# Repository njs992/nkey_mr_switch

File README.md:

# It's a tester. For keyswitches. Named Mr. Switch.
All the pcb and plate files are for KiCad. The plate is just a pcb with no wires.
I ordered stuff from JLCPCB.com. They did a good job, but the plate isn't going to be as cheap as when you order it because of the increased manufacturing time. They'll contact you afterward. It was still pretty cheap.
I use Kailh hotswap sockets and the Adafruit reverse mount LEDs. Currently I've used a SAMD51 Seeduino Xiao, but I think one of the RP2040 ones would be a better fit, as that should make it QMK compatible (with some custom work, obv).
The firmware is garbage right now :) No HID code, debounce issues, LED address issues... It's a work in progress.

# HAVE FUN :)

If you want to use it please leave Mr. Switch's face somewhere on there.
Maybe also give me a shoutout.

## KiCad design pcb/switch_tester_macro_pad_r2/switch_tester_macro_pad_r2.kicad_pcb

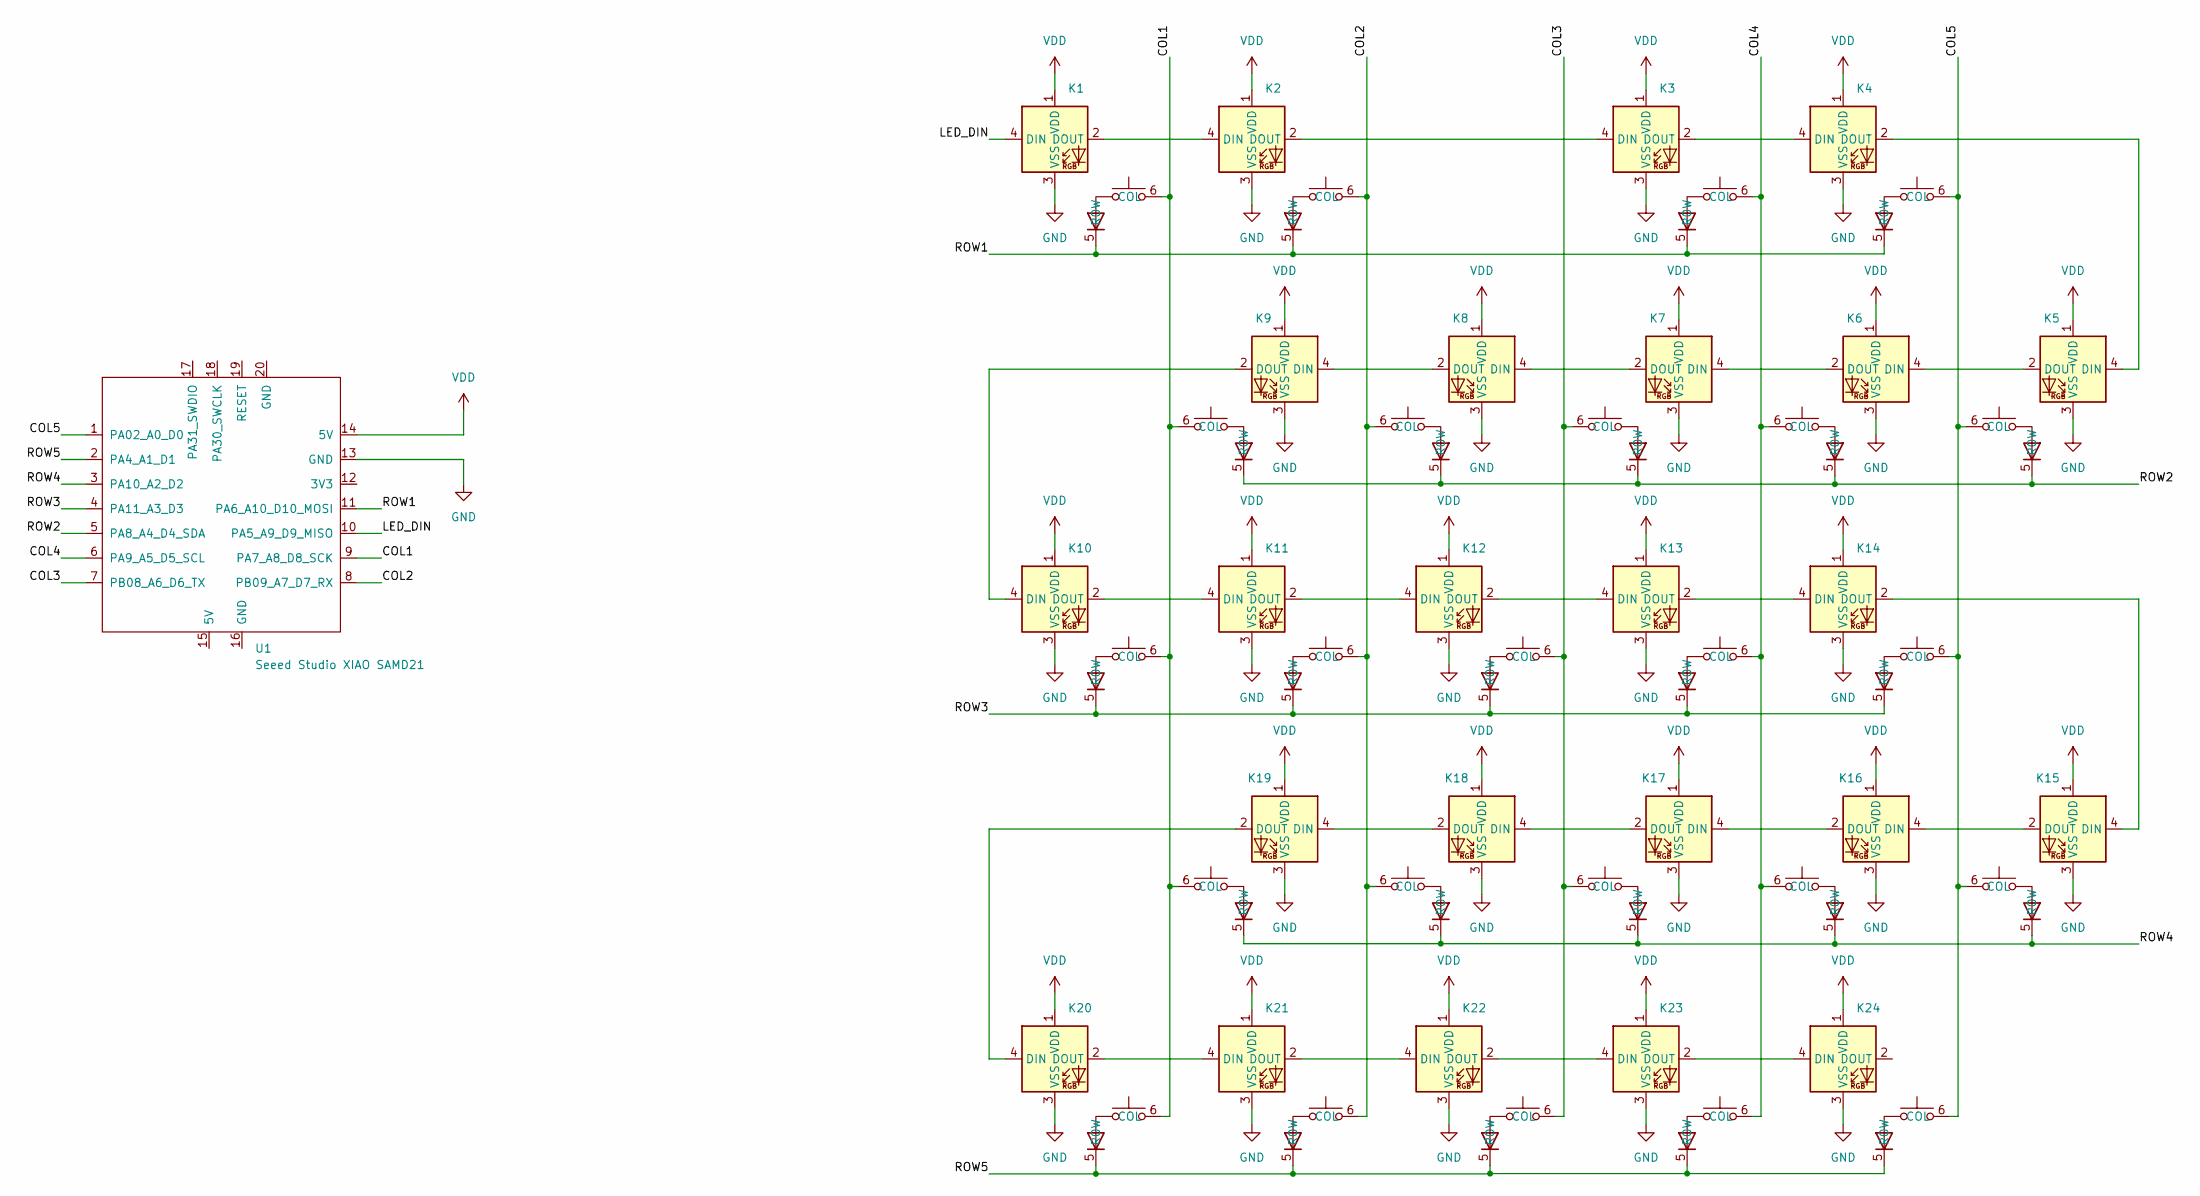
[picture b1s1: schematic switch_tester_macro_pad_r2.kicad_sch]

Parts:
K1, K2, K3, K4, K10, K11, K12, K13, K14, K20, K21, K22, K23, K24: 1U_hl
K5, K6, K7, K8, K9, K15, K16, K17, K18, K19: 1U_hl_backwards
U1: Seeed Studio XIAO SAMD21; XIAO-SAMD21-RP2040-14P-2.54-21X17.8MM (Seeeduino XIAO)

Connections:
/COL1: K1.6 (COL), K9.6 (COL), K10.6 (COL), K19.6 (COL), K20.6 (COL), U1.9 (PA7_A8_D8_SCK)
/COL2: K2.6 (COL), K8.6 (COL), K11.6 (COL), K18.6 (COL), K21.6 (COL), U1.8 (PB09_A7_D7_RX)
/COL3: K7.6 (COL), K12.6 (COL), K17.6 (COL), K22.6 (COL), U1.7 (PB08_A6_D6_TX)
/COL4: K3.6 (COL), K6.6 (COL), K13.6 (COL), K16.6 (COL), K23.6 (COL), U1.6 (PA9_A5_D5_SCL)
/COL5: K4.6 (COL), K5.6 (COL), K14.6 (COL), K15.6 (COL), K24.6 (COL), U1.1 (PA02_A0_D0)
/LED_DIN: K1.4 (DIN), U1.10 (PA5_A9_D9_MISO)
/ROW1: K1.5 (ROW), K2.5 (ROW), K3.5 (ROW), K4.5 (ROW), U1.11 (PA6_A10_D10_MOSI)
/ROW2: K5.5 (ROW), K6.5 (ROW), K7.5 (ROW), K8.5 (ROW), K9.5 (ROW), U1.5 (PA8_A4_D4_SDA)
/ROW3: K10.5 (ROW), K11.5 (ROW), K12.5 (ROW), K13.5 (ROW), K14.5 (ROW), U1.4 (PA11_A3_D3)
/ROW4: K15.5 (ROW), K16.5 (ROW), K17.5 (ROW), K18.5 (ROW), K19.5 (ROW), U1.3 (PA10_A2_D2)
/ROW5: K20.5 (ROW), K21.5 (ROW), K22.5 (ROW), K23.5 (ROW), K24.5 (ROW), U1.2 (PA4_A1_D1)
GND: K1.3 (VSS), K2.3 (VSS), K3.3 (VSS), K4.3 (VSS), K5.3 (VSS), K6.3 (VSS), K7.3 (VSS), K8.3 (VSS), K9.3 (VSS), K10.3 (VSS), K11.3 (VSS), K12.3 (VSS), K13.3 (VSS), K14.3 (VSS), K15.3 (VSS), K16.3 (VSS), K17.3 (VSS), K18.3 (VSS), K19.3 (VSS), K20.3 (VSS), K21.3 (VSS), K22.3 (VSS), K23.3 (VSS), K24.3 (VSS), U1.13 (GND)
unnamed: K1.2 (DOUT), K2.4 (DIN)
unnamed: K2.2 (DOUT), K3.4 (DIN)
unnamed: K3.2 (DOUT), K4.4 (DIN)
unnamed: K4.2 (DOUT), K5.4 (DIN)
unnamed: K5.2 (DOUT), K6.4 (DIN)
unnamed: K6.2 (DOUT), K7.4 (DIN)
unnamed: K7.2 (DOUT), K8.4 (DIN)
unnamed: K8.2 (DOUT), K9.4 (DIN)
unnamed: K9.2 (DOUT), K10.4 (DIN)
unnamed: K10.2 (DOUT), K11.4 (DIN)
unnamed: K11.2 (DOUT), K12.4 (DIN)
unnamed: K12.2 (DOUT), K13.4 (DIN)
unnamed: K13.2 (DOUT), K14.4 (DIN)
unnamed: K14.2 (DOUT), K15.4 (DIN)
unnamed: K15.2 (DOUT), K16.4 (DIN)
unnamed: K16.2 (DOUT), K17.4 (DIN)
unnamed: K17.2 (DOUT), K18.4 (DIN)
unnamed: K18.2 (DOUT), K19.4 (DIN)
unnamed: K19.2 (DOUT), K20.4 (DIN)
unnamed: K20.2 (DOUT), K21.4 (DIN)
unnamed: K21.2 (DOUT), K22.4 (DIN)
unnamed: K22.2 (DOUT), K23.4 (DIN)
unnamed: K23.2 (DOUT), K24.4 (DIN)
VDD: K1.1 (VDD), K2.1 (VDD), K3.1 (VDD), K4.1 (VDD), K5.1 (VDD), K6.1 (VDD), K7.1 (VDD), K8.1 (VDD), K9.1 (VDD), K10.1 (VDD), K11.1 (VDD), K12.1 (VDD), K13.1 (VDD), K14.1 (VDD), K15.1 (VDD), K16.1 (VDD), K17.1 (VDD), K18.1 (VDD), K19.1 (VDD), K20.1 (VDD), K21.1 (VDD), K22.1 (VDD), K23.1 (VDD), K24.1 (VDD), U1.14 (5V)

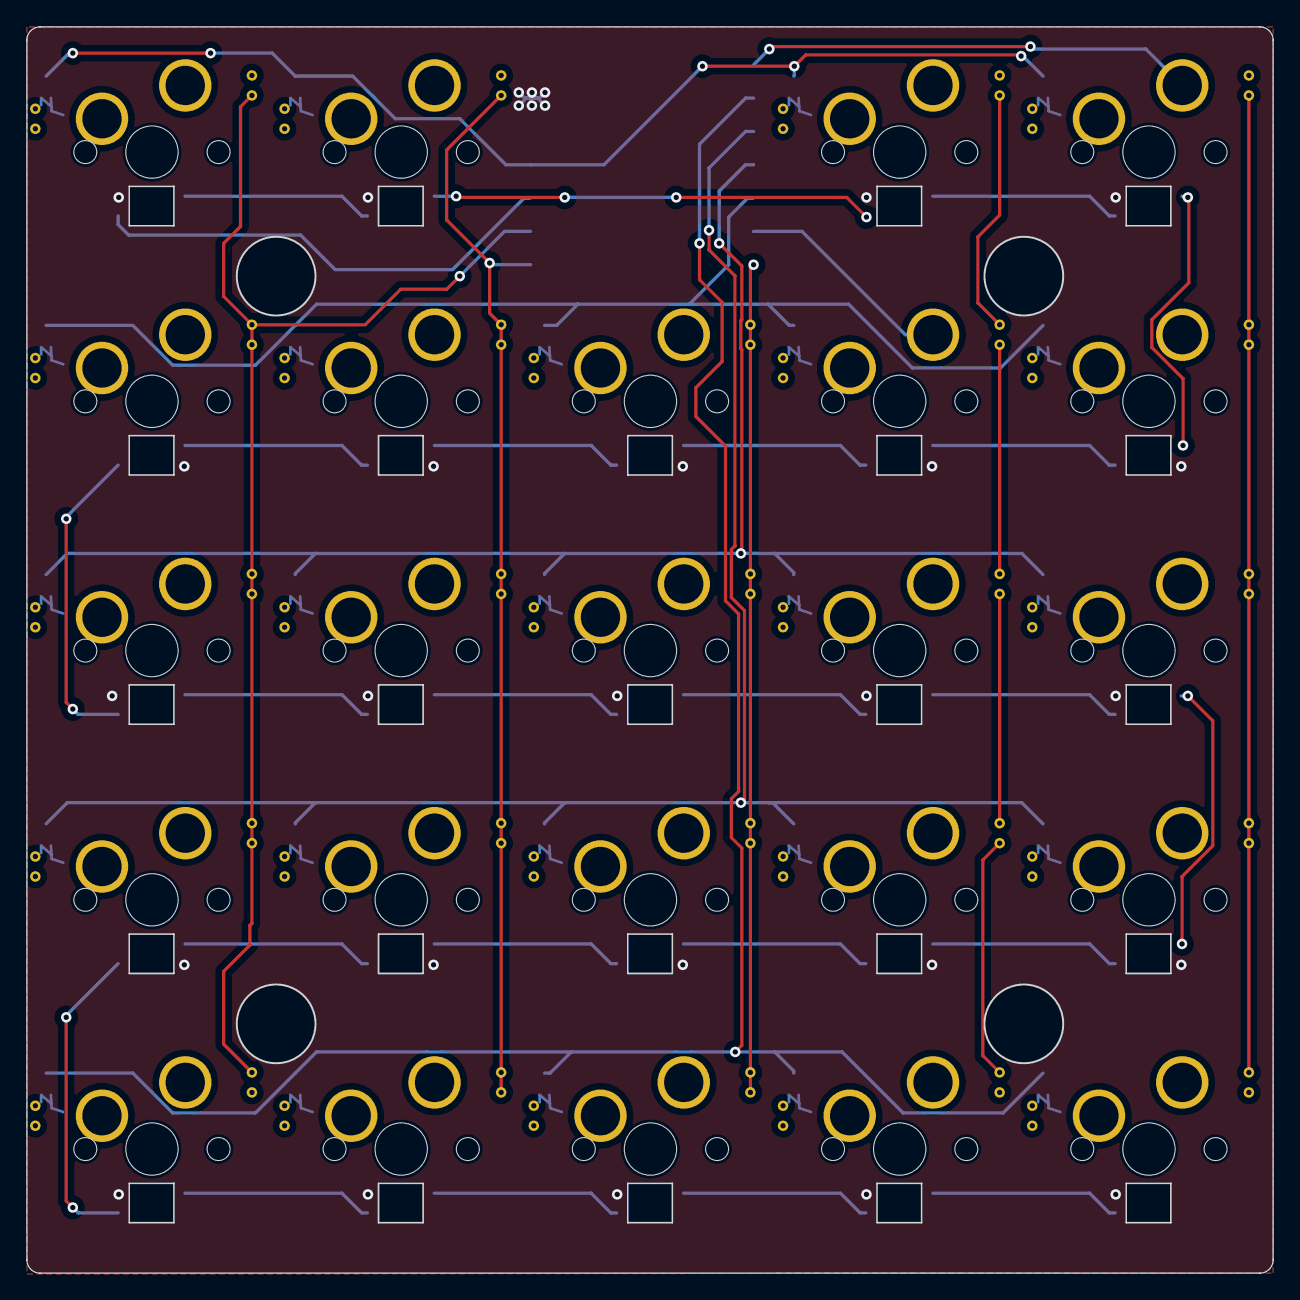
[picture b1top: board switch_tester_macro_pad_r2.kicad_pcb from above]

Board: 2 copper layers, 95.0 x 94.9 mm, 25 parts (1 on the bottom side), 36 nets.

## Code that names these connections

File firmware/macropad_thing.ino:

#include <FastLED.h>
#include <array>
#include <unordered_map>

// Row and Column pin definitions
#define NUM_KEYS 24
#define ROW1 10
#define ROW2 4
#define ROW3 3
#define ROW4 2
#define ROW5 1
#define COL1 8
#define COL2 7
#define COL3 6
#define COL4 5
#define COL5 0

CRGB all_the_colors[] = {
  CRGB::AliceBlue,
  CRGB::Amethyst,
  CRGB::AntiqueWhite,
  CRGB::Aqua,
  CRGB::Aquamarine,
  CRGB::Azure,
  CRGB::Beige,
  CRGB::Bisque,
  CRGB::Black,
  CRGB::BlanchedAlmond,
  CRGB::Blue,
  CRGB::BlueViolet,
  CRGB::Brown,
  CRGB::BurlyWood,
  CRGB::CadetBlue,
  CRGB::Chartreuse,
  CRGB::Chocolate,
  CRGB::Coral,
  CRGB::CornflowerBlue,
  CRGB::Cornsilk,
  CRGB::Crimson,
  CRGB::Cyan,
  CRGB::DarkBlue,
  CRGB::DarkCyan,
  CRGB::DarkGoldenrod,
  CRGB::DarkGray,
  CRGB::DarkGrey,
  CRGB::DarkGreen,
  CRGB::DarkKhaki,
  CRGB::DarkMagenta,
  CRGB::DarkOliveGreen,
  CRGB::DarkOrange,
  CRGB::DarkOrchid,
  CRGB::DarkRed,
  CRGB::DarkSalmon,
  CRGB::DarkSeaGreen,
  CRGB::DarkSlateBlue,
  CRGB::DarkSlateGray,
  CRGB::DarkSlateGrey,
  CRGB::DarkTurquoise,
  CRGB::DarkViolet,
  CRGB::DeepPink,
  CRGB::DeepSkyBlue,
  CRGB::DimGray,
  CRGB::DimGrey,
  CRGB::DodgerBlue,
  CRGB::FireBrick,
  CRGB::FloralWhite,
  CRGB::ForestGreen,
  CRGB::Fuchsia,
  CRGB::Gainsboro,
  CRGB::GhostWhite,
  CRGB::Gold,
  CRGB::Goldenrod,
  CRGB::Gray,
  CRGB::Grey,
  CRGB::Green,
  CRGB::GreenYellow,
  CRGB::Honeydew,
  CRGB::HotPink,
  CRGB::IndianRed,
  CRGB::Indigo,
  CRGB::Ivory,
  CRGB::Khaki,
  CRGB::Lavender,
  CRGB::LavenderBlush,
  CRGB::LawnGreen,
  CRGB::LemonChiffon,
  CRGB::LightBlue,
  CRGB::LightCoral,
  CRGB::LightCyan,
  CRGB::LightGoldenrodYellow,
  CRGB::LightGreen,
  CRGB::LightGrey,
  CRGB::LightPink,
  CRGB::LightSalmon,
  CRGB::LightSeaGreen,
  CRGB::LightSkyBlue,
  CRGB::LightSlateGray,
  CRGB::LightSlateGrey,
  CRGB::LightSteelBlue,
  CRGB::LightYellow,
  CRGB::Lime,
  CRGB::LimeGreen,
  CRGB::Linen,
  CRGB::Magenta,
  CRGB::Maroon,
  CRGB::MediumAquamarine,
  CRGB::MediumBlue,
  CRGB::MediumOrchid,
  CRGB::MediumPurple,
  CRGB::MediumSeaGreen,
  CRGB::MediumSlateBlue,
  CRGB::MediumSpringGreen,
  CRGB::MediumTurquoise,
  CRGB::MediumVioletRed,
  CRGB::MidnightBlue,
  CRGB::MintCream,
  CRGB::MistyRose,
  CRGB::Moccasin,
  CRGB::NavajoWhite,
  CRGB::Navy,
  CRGB::OldLace,
  CRGB::Olive,
  CRGB::OliveDrab,
  CRGB::Orange,
  CRGB::OrangeRed,
  CRGB::Orchid,
  CRGB::PaleGoldenrod,
  CRGB::PaleGreen,
  CRGB::PaleTurquoise,
  CRGB::PaleVioletRed,
  CRGB::PapayaWhip,
  CRGB::PeachPuff,
  CRGB::Peru,
  CRGB::Pink,
  CRGB::Plaid,
  CRGB::Plum,
  CRGB::PowderBlue,
  CRGB::Purple,
  CRGB::Red,
  CRGB::RosyBrown,
  CRGB::RoyalBlue,
  CRGB::SaddleBrown,
  CRGB::Salmon,
  CRGB::SandyBrown,
  CRGB::SeaGreen,
  CRGB::Seashell,
  CRGB::Sienna,
  CRGB::Silver,
  CRGB::SkyBlue,
  CRGB::SlateBlue,
  CRGB::SlateGray,
  CRGB::SlateGrey,
  CRGB::Snow,
  CRGB::SpringGreen,
  CRGB::SteelBlue,
  CRGB::Tan,
  CRGB::Teal,
  CRGB::Thistle,
  CRGB::Tomato,
  CRGB::Turquoise,
  CRGB::Violet,
  CRGB::Wheat,
  CRGB::White,
  CRGB::WhiteSmoke,
  CRGB::Yellow,
  CRGB::YellowGreen
};

const std::array< int, 5 > columns =   { COL1, COL2, COL3, COL4, COL5 };
const std::array< int, 5 > rows = { ROW1, ROW2, ROW3, ROW4, ROW5 };
// const std::array< int, NUM_KEYS > row_order_thing = { ROW1, ROW2,       ROW4, ROW5,
//                                                       ROW5, ROW4, ROW3, ROW2, ROW1,
//                                                       ROW1, ROW2, ROW3, ROW4, ROW5,
//                                                       ROW5, ROW4, ROW3, ROW2, ROW1,
//                                                       ROW1, ROW2, ROW3, ROW4, ROW5 };

int key_idxs[NUM_KEYS] = {0,8,9,18,19,
                          1,7,10,17,20,
                            6,11,16,21,
                          2,5,12,15,22,
                          3,4,13,14,23
                          };

CRGB key_color[NUM_KEYS] = {
  CRGB::Azure,
  CRGB::BlueViolet,
  CRGB::Chocolate,
  CRGB::Crimson,
  CRGB::DeepPink,
  CRGB::Fuchsia,
  CRGB::Goldenrod,
  CRGB::Green,
  CRGB::Indigo,
  CRGB::Lavender,
  CRGB::LimeGreen,
  CRGB::Magenta,
  CRGB::MintCream,
  CRGB::Orange,
  CRGB::PapayaWhip,
  CRGB::Purple,
  CRGB::SteelBlue,
  CRGB::Teal,
  CRGB::Tomato,
  CRGB::Turquoise,
  CRGB::Violet,
  CRGB::Yellow,
  CRGB::Red,
  CRGB::Blue
};

bool key_status[NUM_KEYS];

// key keys[ NUM_KEYS ];

// LED stuff
#define NUM_LEDS NUM_KEYS
#define LED_DIN 9
CRGB macpad_leds[ NUM_LEDS ];

void setup()
{
  FastLED.addLeds< SK6812, LED_DIN, RGB > ( macpad_leds, NUM_LEDS );
  for( const int & row : rows ) { pinMode( row, INPUT ); }
  for( const int & column : columns ) { pinMode( column, OUTPUT ); }
  for( auto & key : key_status ) { key = false; }
}

int cnt{0};

void loop()
{
  // if( scanKeys() ) { updateLeds(); }
  
  // checkThatOneKey();

  // dumbScanKeys();

  // stupidSingleReadLight( ROW1, COL1, 0  );
  // stupidSingleReadLight( ROW1, COL2, 1  );
  // stupidSingleReadLight( ROW1, COL4, 2  );
  // stupidSingleReadLight( ROW1, COL5, 3  );
  // stupidSingleReadLight( ROW2, COL5, 4  );
  // stupidSingleReadLight( ROW2, COL4, 5  );
  // stupidSingleReadLight( ROW2, COL3, 6  );
  // stupidSingleReadLight( ROW2, COL2, 7  );
  // stupidSingleReadLight( ROW2, COL1, 8  );
  // stupidSingleReadLight( ROW3, COL1, 9  );
  // stupidSingleReadLight( ROW3, COL2, 10 );
  // stupidSingleReadLight( ROW3, COL3, 11 );
  // stupidSingleReadLight( ROW3, COL4, 12 );
  // stupidSingleReadLight( ROW3, COL5, 13 );
  // stupidSingleReadLight( ROW4, COL5, 14 );
  // stupidSingleReadLight( ROW4, COL4, 15 );
  // stupidSingleReadLight( ROW4, COL3, 16 );
  // stupidSingleReadLight( ROW4, COL2, 17 );
  // stupidSingleReadLight( ROW4, COL1, 18 );
  // stupidSingleReadLight( ROW5, COL1, 19 );
  // stupidSingleReadLight( ROW5, COL2, 20 );
  // stupidSingleReadLight( ROW5, COL3, 21 );
  // stupidSingleReadLight( ROW5, COL4, 22 );
  // stupidSingleReadLight( ROW5, COL5, 23 );

  // CRGB color_of_the_day = all_the_colors[ (cnt++)%(166-19) ];
  // for( auto & led : macpad_leds ) { led = color_of_the_day; }
  for( auto & led : macpad_leds ) { led = CRGB::Grey; }
  FastLED.setBrightness( 20 );
  FastLED.show();
  // delay(1);
  while(1) { }
}

int key_idx{0};

bool scanKeys()
{
  bool state_change{ false };
  for( const auto & column : columns )
  {
    digitalWrite( column, HIGH );

    for( const auto & row : rows )
    {
      int sensor_reading = digitalRead( row );
      bool reading = (sensor_reading > 800);
      if( key_status[ key_idx ] != reading )
      {
        key_status[ key_idx ] = reading;
        registerKey( key_idx );
        state_change = true;
      }
    }
    digitalWrite( column, LOW );
  }

  key_idx++;
  return state_change;
}

bool registerKey( int key_idx )
{
  bool curr_key_status = key_status[key_idx];
  macpad_leds[key_idx] = curr_key_status ? CRGB::White : CRGB::Black;
  // Also HID stuff?
  return true;
}

bool checkThatOneKey()
{
  digitalWrite(COL3, HIGH);
  int analog_check{ 0 };
  bool check{ false };
  analog_check = analogRead(ROW3);
  if( analog_check > 800 ) { check = true; }
  digitalWrite(COL3, LOW);
  if(check) { macpad_leds[0] = CRGB::Blue; }
  else { macpad_leds[0] = CRGB::Black; }
  FastLED.show();
  return true;
}

bool updateLeds()
{
  FastLED.show();
  return true;
}


bool dumbScanKeys()
{
  dumbColumnRead(COL5);
  delay( 0.1 );
  dumbColumnRead(COL4);
  delay( 0.1 );
  dumbColumnRead(COL3);
  delay( 0.1 );
  dumbColumnRead(COL2);
  delay( 0.1 );
  dumbColumnRead(COL1);
  delay( 0.1 );
}

bool dumbColumnRead( int column )
{
  int col_offset[5] = {0,5,9,14,19};
  int offset_sel = (COL1 == column) ? col_offset[0] :
                   (COL2 == column) ? col_offset[1] :
                   (COL3 == column) ? col_offset[2] :
                   (COL4 == column) ? col_offset[3] :
                   col_offset[4];

  digitalWrite(column, HIGH);
  dumbRowRead( ROW1, key_idxs[offset_sel+0] );
  dumbRowRead( ROW2, key_idxs[offset_sel+1] );
  dumbRowRead( ROW3, key_idxs[offset_sel+2] );
  dumbRowRead( ROW4, key_idxs[offset_sel+3] );
  dumbRowRead( ROW5, key_idxs[offset_sel+4] );
  digitalWrite(column, LOW);
}

bool dumbRowRead( int row, int led )
{
  int temp_read_row{0};
  temp_read_row = analogRead(row);
  if( temp_read_row > 800 ) { macpad_leds[led] = CRGB::Green; }
  else { macpad_leds[led] = CRGB::Black; }
  FastLED.show();
  return true;
}

bool stupidSingleReadLight( int row, int col, int led )
{
  int read_val{ 0 };
  digitalWrite( col, HIGH );
  read_val = analogRead( row );
  digitalWrite( col, LOW );

  if( read_val > 900 ) { macpad_leds[ led ] = key_color[ led ]; }
  else { macpad_leds[ led ] = CRGB::Black; }

  return true;
}

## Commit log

2023-11-11 Actually added readme
2023-11-11 Fixed the readme
2023-11-11 Added the kicad projects for the plate and pcb
2023-11-11 Readme update
2023-11-11 Added firmware, which is currently garbo
